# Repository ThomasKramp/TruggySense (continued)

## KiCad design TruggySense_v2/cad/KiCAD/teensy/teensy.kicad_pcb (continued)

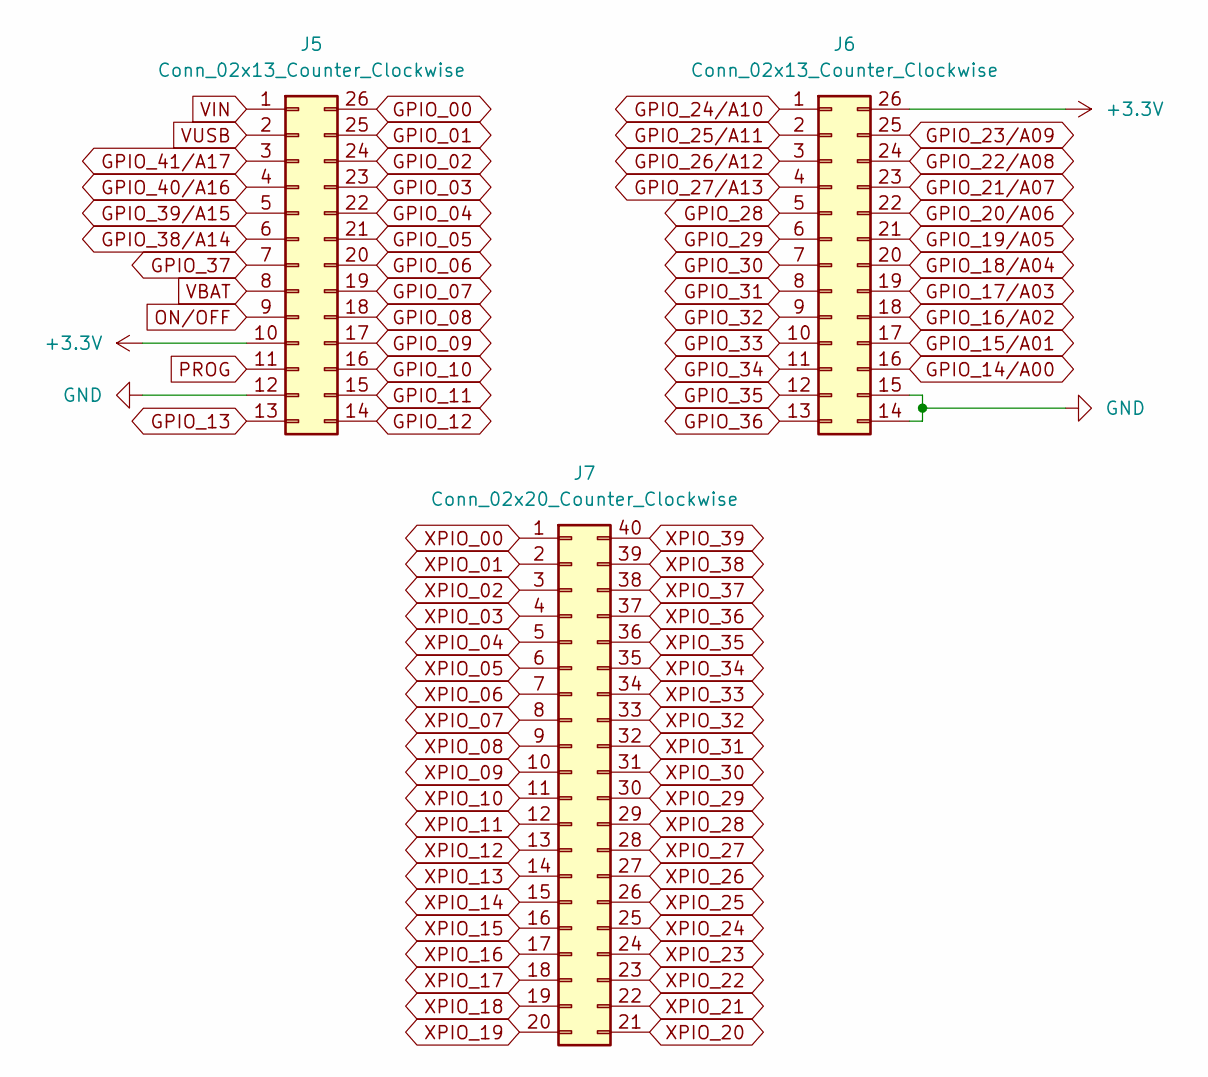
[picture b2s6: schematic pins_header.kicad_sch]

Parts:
J5, J6: Conn_02x13_Counter_Clockwise; PinSocket_2x13_P2.54mm_Vertical
J7: Conn_02x20_Counter_Clockwise; PinHeader_2x20_P2.54mm_Vertical

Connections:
+3.3V: J5.10, J6.26; also elsewhere on the board
FLS_32_B2: J5.11; also elsewhere on the board
GND: J5.12, J6.14, J6.15; also elsewhere on the board
GPIO_00: J5.26; also elsewhere on the board
GPIO_01: J5.25; also elsewhere on the board
GPIO_02: J5.24; also elsewhere on the board
GPIO_03: J5.23; also elsewhere on the board
GPIO_04: J5.22; also elsewhere on the board
GPIO_05: J5.21; also elsewhere on the board
GPIO_06: J5.20; also elsewhere on the board
GPIO_07: J5.19; also elsewhere on the board
GPIO_08: J5.18; also elsewhere on the board
GPIO_09: J5.17; also elsewhere on the board
GPIO_10: J5.16; also elsewhere on the board
GPIO_11: J5.15; also elsewhere on the board
GPIO_12: J5.14; also elsewhere on the board
GPIO_13: J5.13; also elsewhere on the board
GPIO_14/A00: J6.16; also elsewhere on the board
GPIO_15/A01: J6.17; also elsewhere on the board
GPIO_16/A02: J6.18; also elsewhere on the board
GPIO_17/A03: J6.19; also elsewhere on the board
GPIO_18/A04: J6.20; also elsewhere on the board
GPIO_19/A05: J6.21; also elsewhere on the board
GPIO_20/A06: J6.22; also elsewhere on the board
GPIO_21/A07: J6.23; also elsewhere on the board
GPIO_22/A08: J6.24; also elsewhere on the board
GPIO_23/A09: J6.25; also elsewhere on the board
GPIO_24/A10: J6.1; also elsewhere on the board
GPIO_25/A11: J6.2; also elsewhere on the board
GPIO_26/A12: J6.3; also elsewhere on the board
GPIO_27/A13: J6.4; also elsewhere on the board
GPIO_28: J6.5; also elsewhere on the board
GPIO_29: J6.6; also elsewhere on the board
GPIO_30: J6.7; also elsewhere on the board
GPIO_31: J6.8; also elsewhere on the board
GPIO_32: J6.9; also elsewhere on the board
GPIO_33: J6.10; also elsewhere on the board
GPIO_34: J6.11; also elsewhere on the board
GPIO_35: J6.12; also elsewhere on the board
GPIO_36: J6.13; also elsewhere on the board
GPIO_37: J5.7; also elsewhere on the board
GPIO_38/A14: J5.6; also elsewhere on the board
GPIO_39/A15: J5.5; also elsewhere on the board
GPIO_40/A16: J5.4; also elsewhere on the board
GPIO_41/A17: J5.3; also elsewhere on the board
ON/OFF: J5.9; also elsewhere on the board
VBAT: J5.8; also elsewhere on the board
VIN: J5.1; also elsewhere on the board
VUSB: J5.2; also elsewhere on the board
XPIO_00: J7.1; also elsewhere on the board
XPIO_01: J7.2; also elsewhere on the board
XPIO_02: J7.3; also elsewhere on the board
XPIO_03: J7.4; also elsewhere on the board
XPIO_04: J7.5; also elsewhere on the board
XPIO_05: J7.6; also elsewhere on the board
XPIO_06: J7.7; also elsewhere on the board
XPIO_07: J7.8; also elsewhere on the board
XPIO_08: J7.9; also elsewhere on the board
XPIO_09: J7.10; also elsewhere on the board
XPIO_10: J7.11; also elsewhere on the board
XPIO_11: J7.12; also elsewhere on the board
XPIO_12: J7.13; also elsewhere on the board
XPIO_13: J7.14; also elsewhere on the board
XPIO_14: J7.15; also elsewhere on the board
XPIO_15: J7.16; also elsewhere on the board
XPIO_16: J7.17; also elsewhere on the board
XPIO_17: J7.18; also elsewhere on the board
XPIO_18: J7.19; also elsewhere on the board
XPIO_19: J7.20; also elsewhere on the board
XPIO_20: J7.21; also elsewhere on the board
XPIO_21: J7.22; also elsewhere on the board
XPIO_22: J7.23; also elsewhere on the board
XPIO_23: J7.24; also elsewhere on the board
XPIO_24: J7.25; also elsewhere on the board
XPIO_25: J7.26; also elsewhere on the board
XPIO_26: J7.27; also elsewhere on the board
XPIO_27: J7.28; also elsewhere on the board
XPIO_28: J7.29; also elsewhere on the board
XPIO_29: J7.30; also elsewhere on the board
XPIO_30: J7.31; also elsewhere on the board
XPIO_31: J7.32; also elsewhere on the board
XPIO_32: J7.33; also elsewhere on the board
XPIO_33: J7.34; also elsewhere on the board
XPIO_34: J7.35; also elsewhere on the board
XPIO_35: J7.36; also elsewhere on the board
XPIO_36: J7.37; also elsewhere on the board
XPIO_37: J7.38; also elsewhere on the board
XPIO_38: J7.39; also elsewhere on the board
XPIO_39: J7.40; also elsewhere on the board

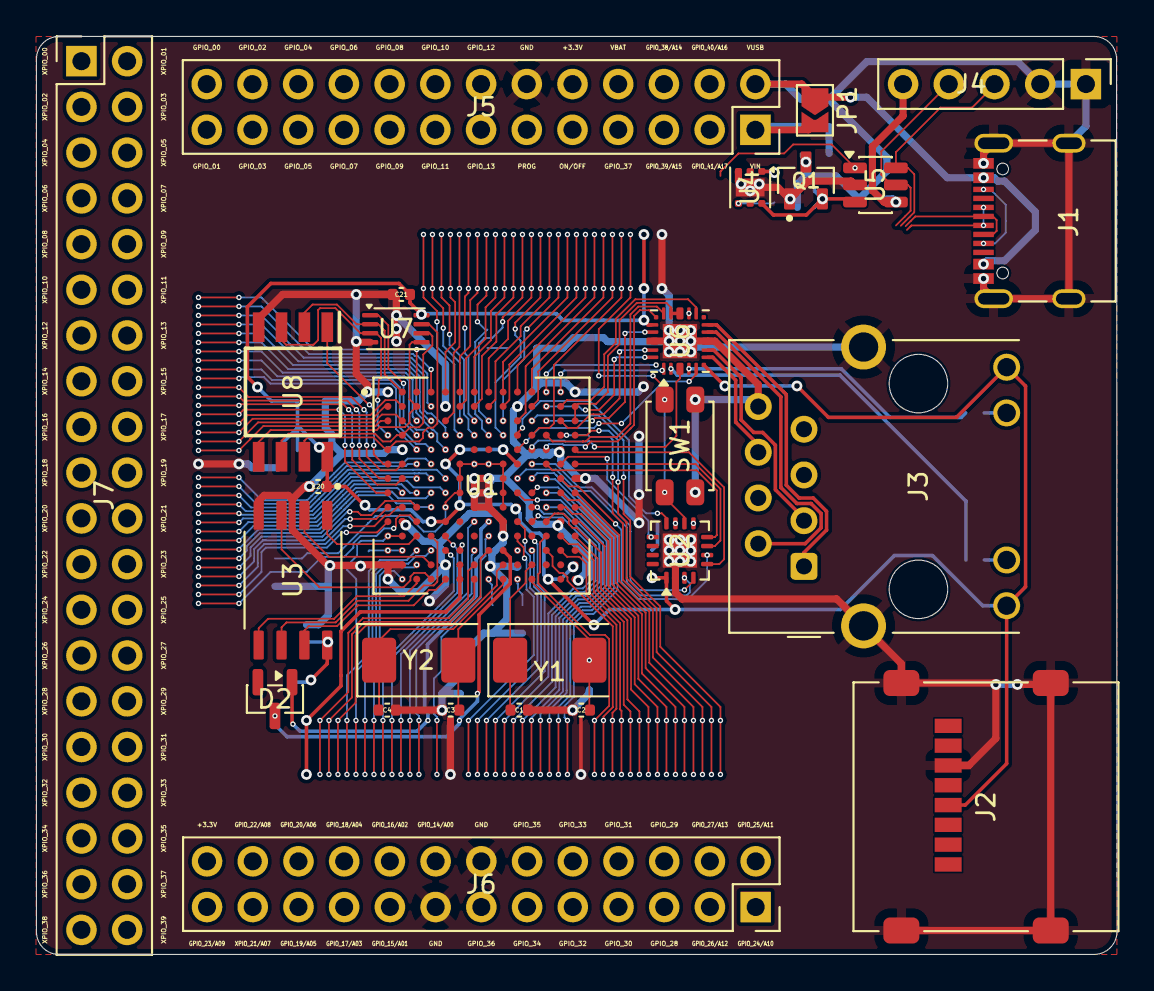
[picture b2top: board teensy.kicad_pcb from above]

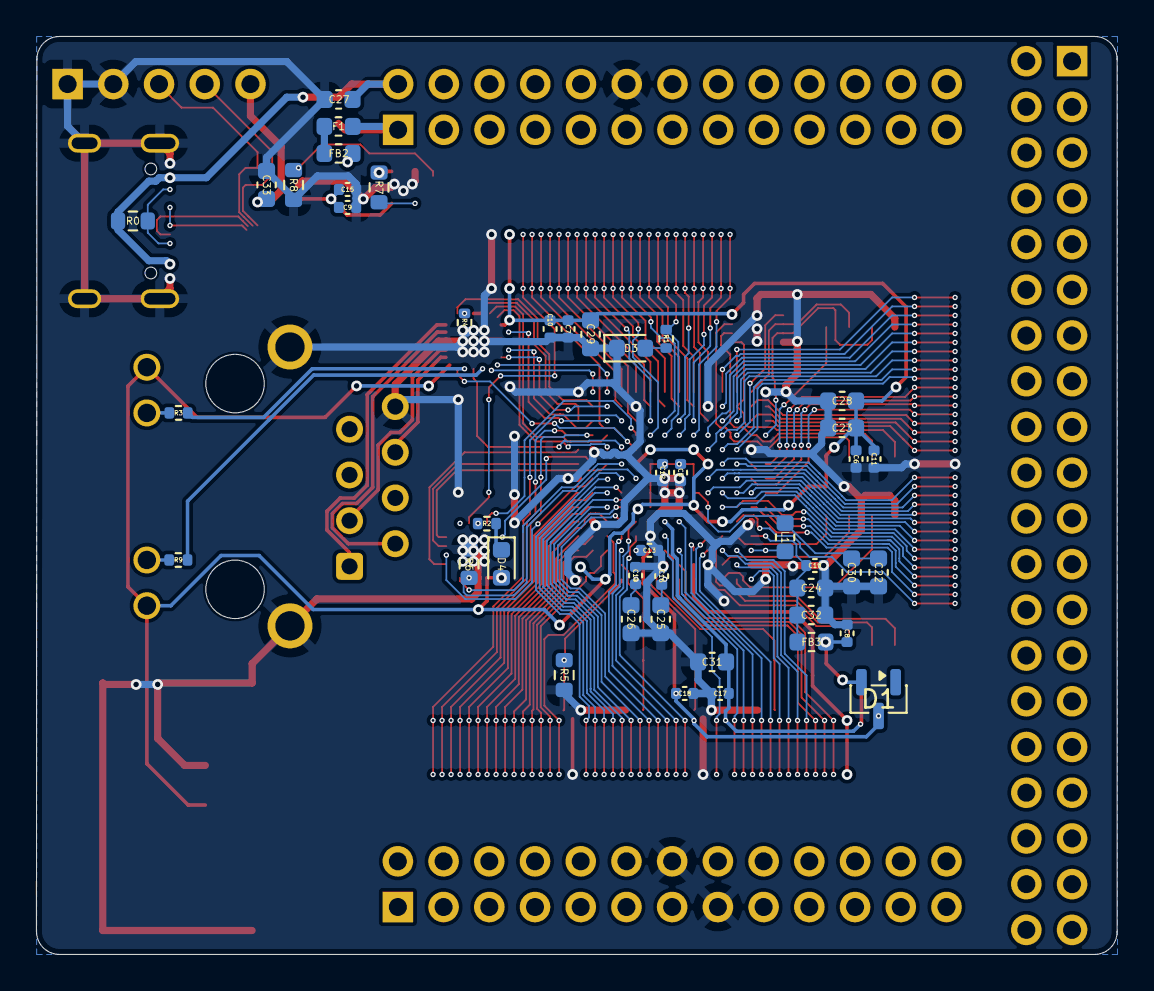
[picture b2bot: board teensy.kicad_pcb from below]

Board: 2 copper layers, 60.0 x 51.0 mm, 71 parts (44 on the bottom side), 164 nets.

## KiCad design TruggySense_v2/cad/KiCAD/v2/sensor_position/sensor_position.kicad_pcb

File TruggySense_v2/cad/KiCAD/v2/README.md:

## KiCAD

- **1_logic_board**:        The board-design and electrical schematic that contains the LLC, most sensors and connector points.
- **2_power_board**:        The board-design and electrical schematic that contains the connection to the battery and provides power to the motors.
- **sensor_position**:      The board-design and electrical schematic of the GNSS/GPS module.
- **sensor_temperature**:   The board-design and electrical schematic of the temperature sensor.

- **io_protection_buffer**: An electrical schematic of the protection buffer, for certain input purposes, used in the logic board.
- **io_protection_input**:  An electrical schematic for the input protection, used in the logic board.
- **io_protection_output**: An electrical schematic for the output protection, used in the logic board.

- **layout_nrf24l01**:      A generic board-layout for nRF24L01 modules, used in the logic board.
- **layout_pim448**:        A generic board-layout for motion sensor, used in the logic board.

- **recreation_ina219**:    A recreation of both the electrical schematic and board-design, for the low-current sensor.
- **recreation_lm2596**:    A recreation of both the electrical schematic and board-design, for the voltage converter (5V --> 3V3).

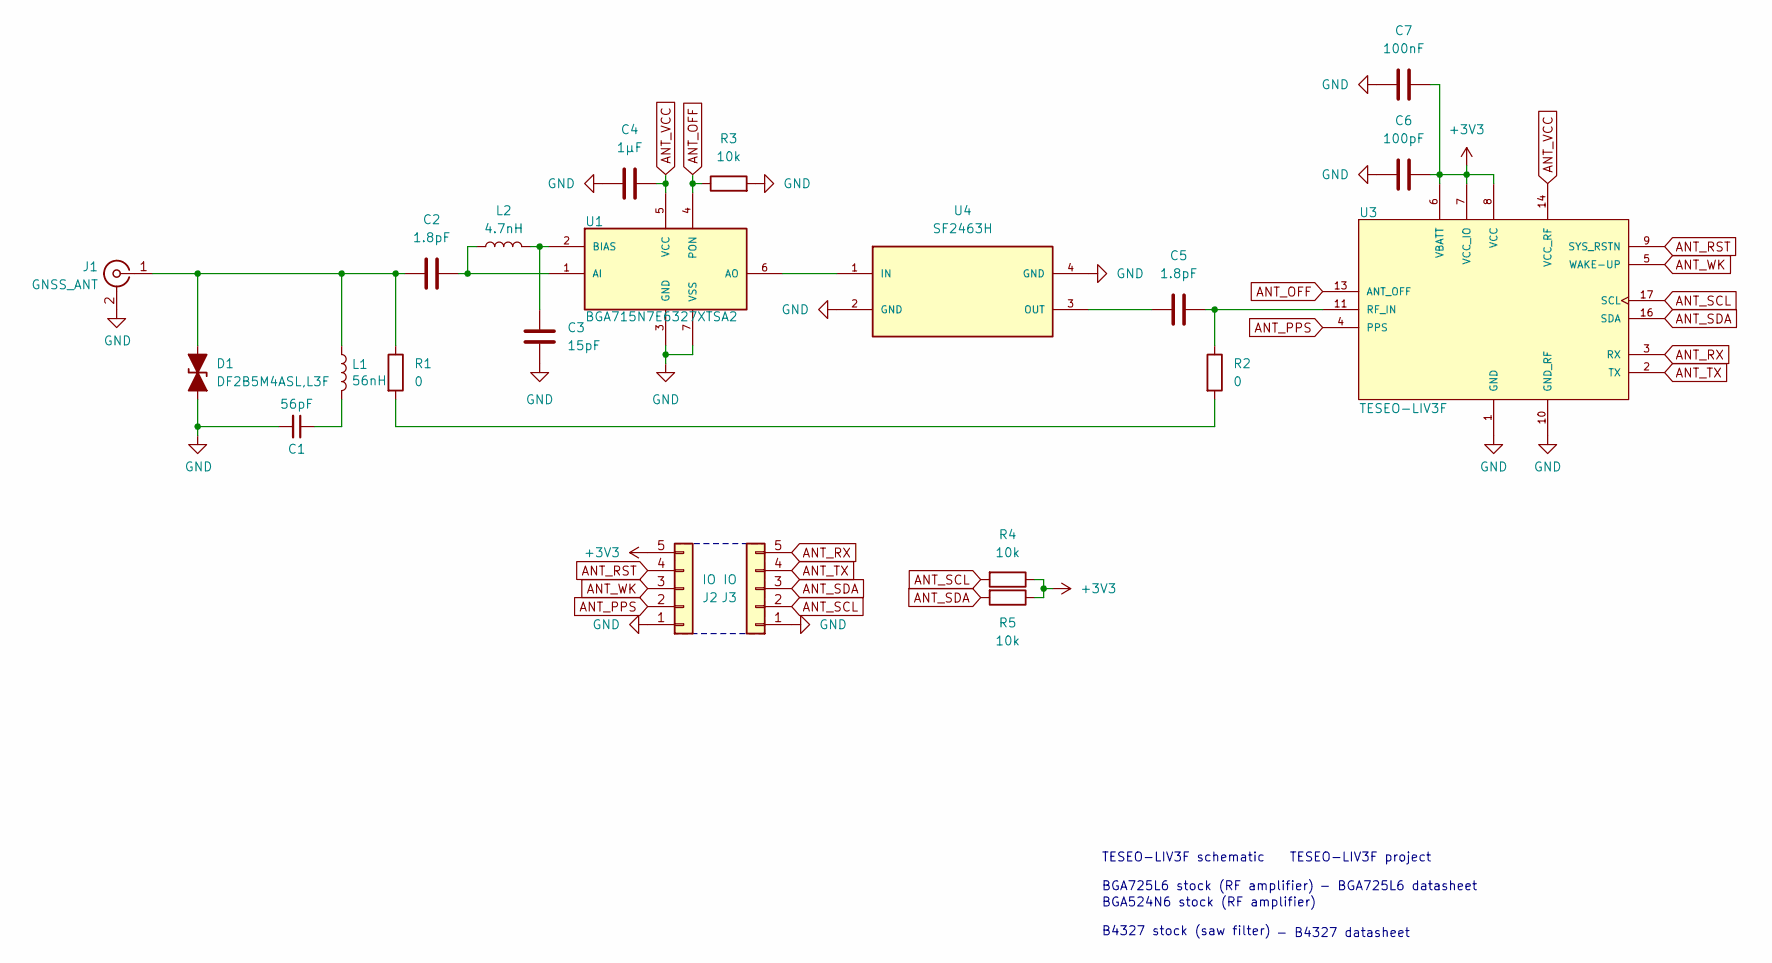
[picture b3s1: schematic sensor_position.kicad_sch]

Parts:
C1: 56pF; C_0805_2012Metric_Pad1.18x1.45mm_HandSolder; MPN GRM1555C1H560JA01D; Digi-Key_PN 490-1288-1-ND
C2, C5: 1.8pF; C_0805_2012Metric_Pad1.18x1.45mm_HandSolder
C3: 15pF; C_0805_2012Metric_Pad1.18x1.45mm_HandSolder
C4: 1µF; C_0805_2012Metric_Pad1.18x1.45mm_HandSolder
C6: 100pF; C_0805_2012Metric_Pad1.18x1.45mm_HandSolder
C7: 100nF; C_0805_2012Metric_Pad1.18x1.45mm_HandSolder
D1: DF2B5M4ASL,L3F; DF2B5M4ASL
J1: GNSS_ANT; SMA_Molex_73251-1153_EdgeMount_Horizontal
J2, J3: IO; PinHeader_1x05_P2.54mm_Vertical
L1: 56nH; L_0805_2012Metric_Pad1.05x1.20mm_HandSolder; MPN 744784156A; Digi-Key_PN 732-6242-1-ND
L2: 4.7nH; L_0805_2012Metric_Pad1.05x1.20mm_HandSolder
R1, R2: 0; R_0805_2012Metric_Pad1.20x1.40mm_HandSolder
R3, R4, R5: 10k; R_0805_2012Metric_Pad1.20x1.40mm_HandSolder
U1: BGA715N7E6327XTSA2; AMP_BGA715N7
U3: TESEO-LIV3F
U4: SF2463H

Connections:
+3V3: C6.2, C7.1, J2.5, R4.1, R5.1, U3.6 (VBATT), U3.7 (VCC_IO), U3.8 (VCC)
ANT_OFF: R3.1, U1.4 (PON), U3.13 (ANT_OFF)
ANT_PPS: J2.2, U3.4 (PPS)
ANT_RST: J2.4, U3.9 (SYS_RSTN)
ANT_RX: J3.5, U3.3 (RX)
ANT_SCL: J3.2, R4.2, U3.17 (SCL)
ANT_SDA: J3.3, R5.2, U3.16 (SDA)
ANT_TX: J3.4, U3.2 (TX)
ANT_VCC: C4.2, U1.5 (VCC), U3.14 (VCC_RF)
ANT_WK: J2.3, U3.5 (WAKE-UP)
GND: C1.2, C3.1, C4.1, C6.1, C7.2, D1.1 (A1), J1.2 (Ext), J2.1, J3.1, R3.2, U1.3 (GND), U1.7 (VSS), U3.1 (GND), U3.10 (GND_RF), U3.12 (GND_RF), U4.2 (GND), U4.4 (GND)
unnamed: C1.1, L1.2
unnamed: C2.1, D1.2 (A2), J1.1 (In), L1.1, R1.1
unnamed: R1.2, R2.2
unnamed: C2.2, L2.1, U1.1 (AI)
unnamed: U1.6 (AO), U4.1 (IN)
unnamed: C3.2, L2.2, U1.2 (BIAS)
unnamed: C5.2, R2.1, U3.11 (RF_IN)
unnamed: C5.1, U4.3 (OUT)

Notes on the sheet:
BGA725L6 stock (RF amplifier)
- BGA725L6 datasheet
BGA524N6 stock (RF amplifier)
TESEO-LIV3F project
B4327 stock (saw filter)
- B4327 datasheet
TESEO-LIV3F schematic

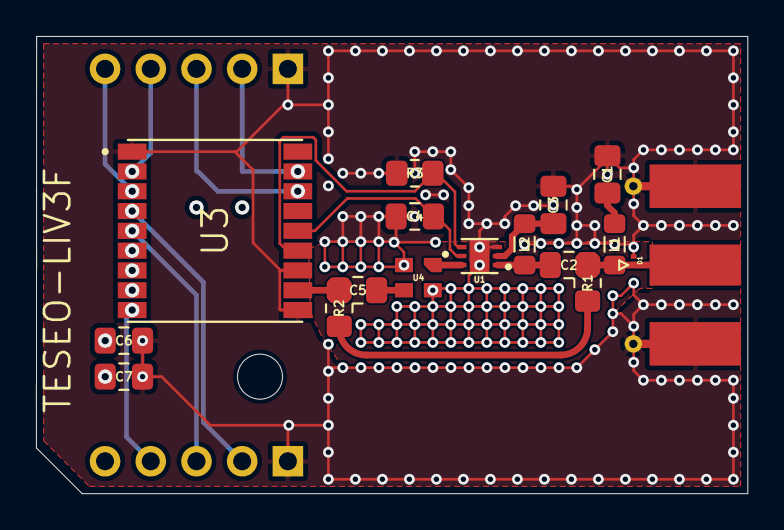
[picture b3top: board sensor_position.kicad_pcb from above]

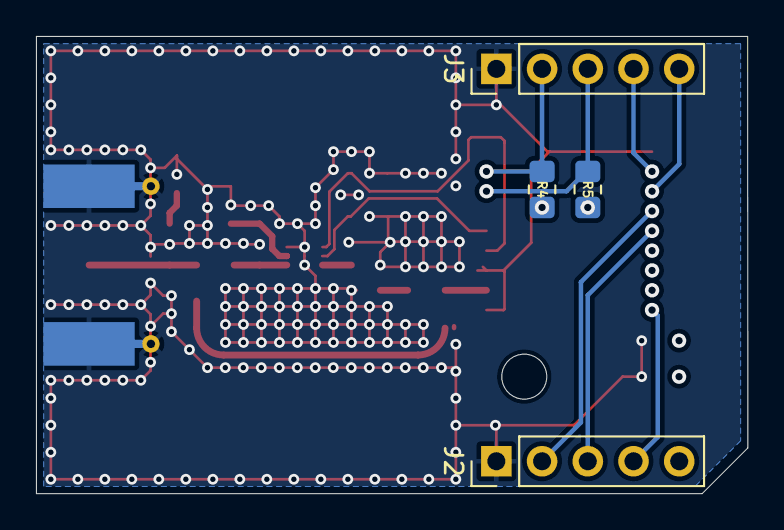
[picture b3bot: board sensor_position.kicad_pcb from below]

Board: 4 copper layers, 39.5 x 25.4 mm, 21 parts (4 on the bottom side), 19 nets.

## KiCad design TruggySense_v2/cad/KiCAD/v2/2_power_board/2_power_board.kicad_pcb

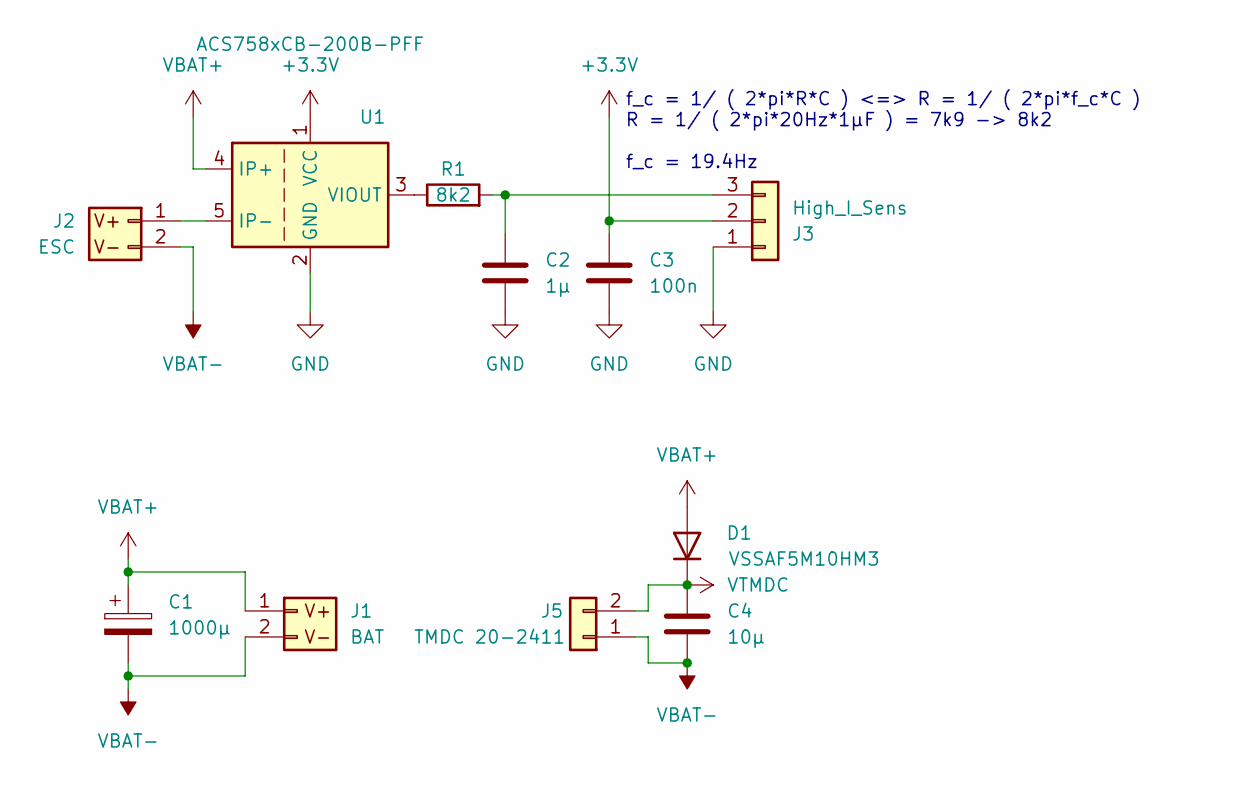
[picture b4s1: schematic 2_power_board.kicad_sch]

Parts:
C1: 1000µ; CP_Radial_D16.0mm_P7.50mm
C2: 1µ; C_0805_2012Metric_Pad1.18x1.45mm_HandSolder
C3: 100n; C_0805_2012Metric_Pad1.18x1.45mm_HandSolder
C4: 10µ; C_0805_2012Metric_Pad1.18x1.45mm_HandSolder
D1: VSSAF5M10HM3; DIOM5226X100N
J1: BAT; EC5_cable_pads
J2: ESC; EC5_cable_pads
J3: High_I_Sens; JST_XH_B3B-XH-A_1x03_P2.50mm_Vertical
J5: TMDC 20-2411; TerminalBlock_Phoenix_MKDS-1,5-2-5.08_1x02_P5.08mm_Horizont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
R1: 8k2; R_0805_2012Metric_Pad1.20x1.40mm_HandSolder
U1: ACS758xCB-200B-PFF; Allegro_CB_PFF

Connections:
+3.3V: C3.2, J3.2, U1.1 (VCC)
GND: C2.1, C3.1, J3.1, U1.2 (GND)
unnamed: J2.1 (V+), U1.5 (IP-)
unnamed: C2.2, J3.3, R1.2
unnamed: R1.1, U1.3 (VIOUT)
VBAT+: C1.1, D1.2 (A), J1.1 (V+), U1.4 (IP+)
VBAT-: C1.2, C4.2, J1.2 (V-), J2.2 (V-), J5.1
VTMDC: C4.1, D1.1 (K), J5.2

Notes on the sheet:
f_c = 1/ ( 2*pi*R*C ) <=> R = 1/ ( 2*pi*f_c*C ) R = 1/ ( 2*pi*20Hz*1µF ) = 7k9 -> 8k2 f_c = 19.4Hz

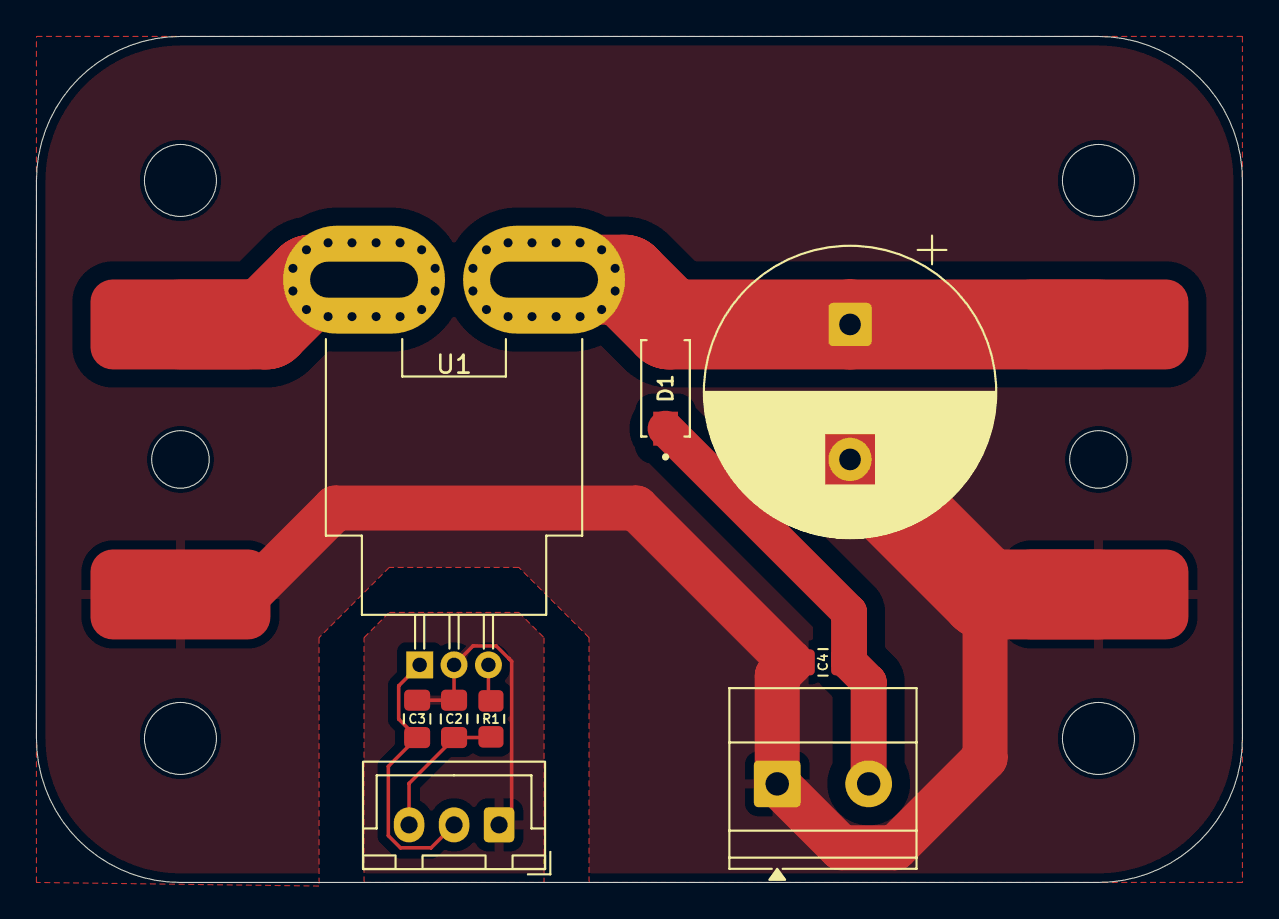
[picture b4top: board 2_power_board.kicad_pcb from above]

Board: 2 copper layers, 67.0 x 47.0 mm, 11 parts (0 on the bottom side), 8 nets.

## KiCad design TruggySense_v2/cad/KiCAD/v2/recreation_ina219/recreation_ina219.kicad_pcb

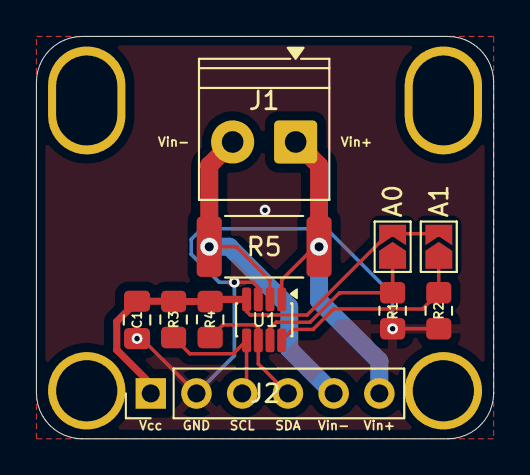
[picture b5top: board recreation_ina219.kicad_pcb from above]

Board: 2 copper layers, 25.4 x 22.4 mm, 11 parts (0 on the bottom side), 8 nets.

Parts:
C1: 100nF; C_0805_2012Metric_Pad1.18x1.45mm_HandSolder
J1: IN; TerminalBlock_Phoenix_PT-1,5-2-3.5-H_1x02_P3.50mm_Horizontal
J2: IO; PinHeader_1x06_P2.54mm_Vertical
JP1: A0; SolderJumper-2_P1.3mm_Open_TrianglePad1.0x1.5mm
JP2: A1; SolderJumper-2_P1.3mm_Open_TrianglePad1.0x1.5mm
R1, R2: 10k; R_0805_2012Metric_Pad1.20x1.40mm_HandSolder
R3, R4: 4k7; R_0805_2012Metric_Pad1.20x1.40mm_HandSolder
R5: 100m; R_2512_6332Metric_Pad1.40x3.35mm_HandSolder
U1: INA219AxDCN; SOT-23-8

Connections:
+3V3: C1.1, J2.1, JP1.2 (B), JP2.2 (B), R3.1, R4.1, U1.4 (VS)
GND: C1.2, J2.2, R1.2, R2.2, U1.3 (GND)
IN+: J1.1, J2.6, R5.1, U1.1 (IN+)
IN-: J1.2, J2.5, R5.2, U1.2 (IN-)
unnamed: JP1.1 (A), R1.1, U1.7 (A0)
unnamed: JP2.1 (A), R2.1, U1.8 (A1)
SCL: J2.3, R3.2, U1.5 (SCL)
SDA: J2.4, R4.2, U1.6 (SDA)

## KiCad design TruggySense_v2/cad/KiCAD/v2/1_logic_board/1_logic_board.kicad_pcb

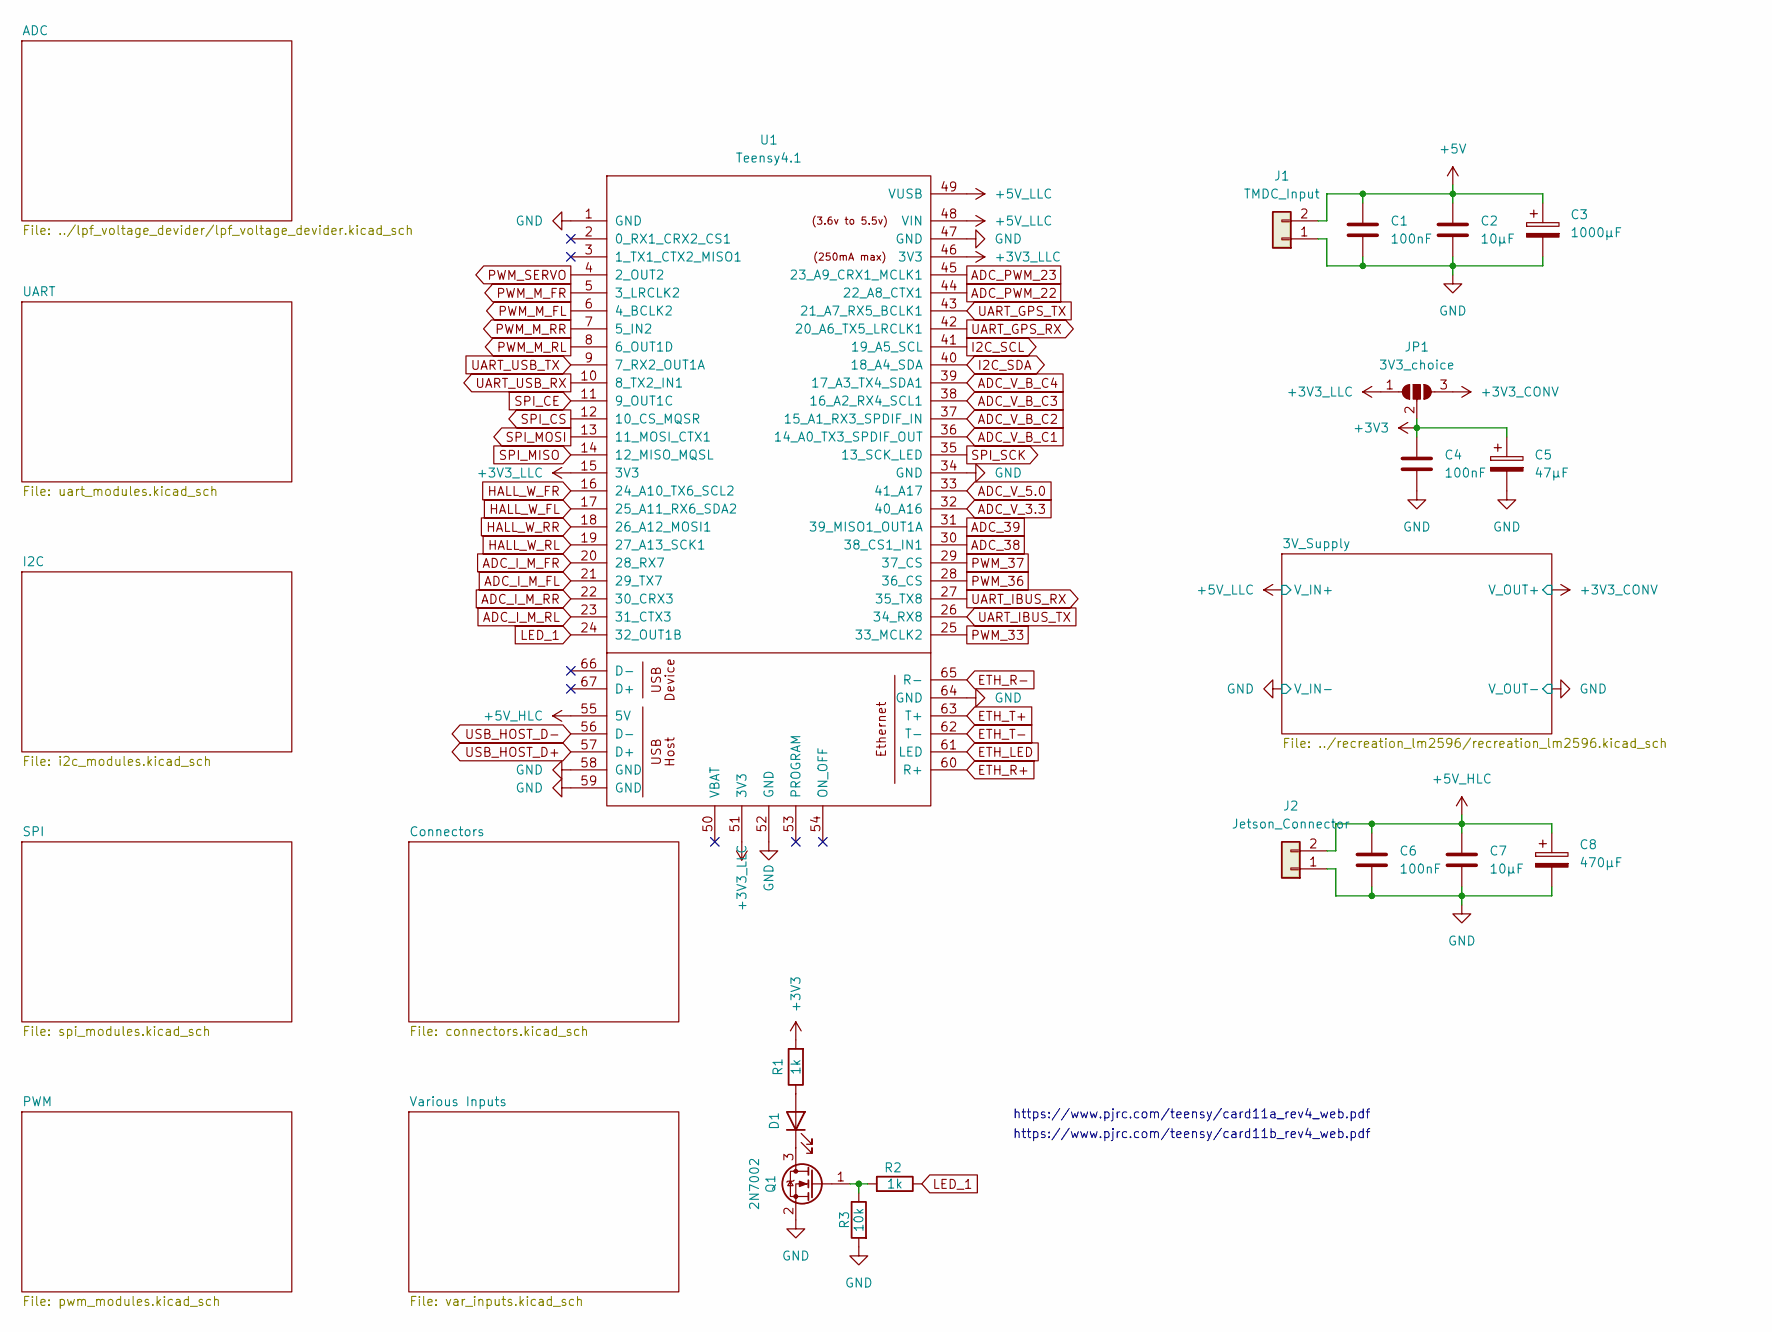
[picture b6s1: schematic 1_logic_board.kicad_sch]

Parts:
C1, C4, C6: 100nF; C_0805_2012Metric_Pad1.18x1.45mm_HandSolder
C2, C7: 10µF; C_0805_2012Metric_Pad1.18x1.45mm_HandSolder
C3: 1000µF; CP_Radial_D10.0mm_P5.00mm
C5: 47µF; CP_Radial_D8.0mm_P3.50mm
C8: 470µF; CP_Radial_D10.0mm_P5.00mm
D1: LED; LED_PLCC-2_3.4x3.0mm_AK
J1: TMDC_Input; TerminalBlock_Phoenix_MKDS-1,5-2-5.08_1x02_P5.08mm_Horizont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
J2: Jetson_Connector; TerminalBlock_Phoenix_MKDS-1,5-2-5.08_1x02_P5.08mm_Horizont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
JP1: 3V3_choice; SolderJumper-3_P2.0mm_Open_TrianglePad1.0x1.5mm_NumberLabels
Q1: 2N7002; SOT-23
R1, R2: 1k; R_0805_2012Metric_Pad1.20x1.40mm_HandSolder
R3: 10k; R_0805_2012Metric_Pad1.20x1.40mm_HandSolder
U1: Teensy4.1; Teensy41

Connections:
+3V3: C4.1, C5.1, JP1.2 (C), R1.2; also elsewhere on the board
+3V3_CONV: JP1.3 (B); also elsewhere on the board
+3V3_LLC: JP1.1 (A), U1.15 (3V3), U1.46 (3V3), U1.51 (3V3)
+5V: C1.1, C2.1, C3.1, J1.2; also elsewhere on the board
+5V_HLC: C6.1, C7.1, C8.1, J2.2, U1.55 (5V); also elsewhere on the board
+5V_LLC: U1.48 (VIN), U1.49 (VUSB); also elsewhere on the board
ADC_38: U1.30 (38_CS1_IN1); also elsewhere on the board
ADC_39: U1.31 (39_MISO1_OUT1A); also elsewhere on the board
ADC_I_M_FL: U1.21 (29_TX7); also elsewhere on the board
ADC_I_M_FR: U1.20 (28_RX7); also elsewhere on the board
ADC_I_M_RL: U1.23 (31_CTX3); also elsewhere on the board
ADC_I_M_RR: U1.22 (30_CRX3); also elsewhere on the board
ADC_PWM_22: U1.44 (22_A8_CTX1); also elsewhere on the board
ADC_PWM_23: U1.45 (23_A9_CRX1_MCLK1); also elsewhere on the board
ADC_V_3.3: U1.32 (40_A16); also elsewhere on the board
ADC_V_5.0: U1.33 (41_A17); also elsewhere on the board
ADC_V_B_C1: U1.36 (14_A0_TX3_SPDIF_OUT); also elsewhere on the board
ADC_V_B_C2: U1.37 (15_A1_RX3_SPDIF_IN); also elsewhere on the board
ADC_V_B_C3: U1.38 (16_A2_RX4_SCL1); also elsewhere on the board
ADC_V_B_C4: U1.39 (17_A3_TX4_SDA1); also elsewhere on the board
ETH_LED: U1.61 (LED); also elsewhere on the board
ETH_R+: U1.60 (R+); also elsewhere on the board
ETH_R-: U1.65 (R-); also elsewhere on the board
ETH_T+: U1.63 (T+); also elsewhere on the board
ETH_T-: U1.62 (T-); also elsewhere on the board
GND: C1.2, C2.2, C3.2, C4.2, C5.2, C6.2, C7.2, C8.2, J1.1, J2.1, Q1.2 (S), R3.2, U1.1 (GND), U1.34 (GND), U1.47 (GND), U1.52 (GND), U1.58 (GND), U1.59 (GND), U1.64 (GND); also elsewhere on the board
HALL_W_FL: U1.17 (25_A11_RX6_SDA2); also elsewhere on the board
HALL_W_FR: U1.16 (24_A10_TX6_SCL2); also elsewhere on the board
HALL_W_RL: U1.19 (27_A13_SCK1); also elsewhere on the board
HALL_W_RR: U1.18 (26_A12_MOSI1); also elsewhere on the board
I2C_SCL: U1.41 (19_A5_SCL); also elsewhere on the board
I2C_SDA: U1.40 (18_A4_SDA); also elsewhere on the board
LED_1: R2.1, U1.24 (32_OUT1B); also elsewhere on the board
unnamed: D1.2 (A), R1.1
unnamed: D1.1 (K), Q1.3 (D)
unnamed: Q1.1 (G), R2.2, R3.1
PWM_33: U1.25 (33_MCLK2); also elsewhere on the board
PWM_36: U1.28 (36_CS); also elsewhere on the board
PWM_37: U1.29 (37_CS); also elsewhere on the board
PWM_M_FL: U1.6 (4_BCLK2); also elsewhere on the board
PWM_M_FR: U1.5 (3_LRCLK2); also elsewhere on the board
PWM_M_RL: U1.8 (6_OUT1D); also elsewhere on the board
PWM_M_RR: U1.7 (5_IN2); also elsewhere on the board
PWM_SERVO: U1.4 (2_OUT2); also elsewhere on the board
SPI_CE: U1.11 (9_OUT1C); also elsewhere on the board
SPI_CS: U1.12 (10_CS_MQSR); also elsewhere on the board
SPI_MISO: U1.14 (12_MISO_MQSL); also elsewhere on the board
SPI_MOSI: U1.13 (11_MOSI_CTX1); also elsewhere on the board
SPI_SCK: U1.35 (13_SCK_LED); also elsewhere on the board
UART_GPS_RX: U1.42 (20_A6_TX5_LRCLK1); also elsewhere on the board
UART_GPS_TX: U1.43 (21_A7_RX5_BCLK1); also elsewhere on the board
UART_IBUS_RX: U1.27 (35_TX8); also elsewhere on the board
UART_IBUS_TX: U1.26 (34_RX8); also elsewhere on the board
UART_USB_RX: U1.10 (8_TX2_IN1); also elsewhere on the board
UART_USB_TX: U1.9 (7_RX2_OUT1A); also elsewhere on the board
USB_HOST_D+: U1.57 (D+); also elsewhere on the board
USB_HOST_D-: U1.56 (D-); also elsewhere on the board

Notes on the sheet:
https://www.pjrc.com/teensy/card11b_rev4_web.pdf
https://www.pjrc.com/teensy/card11a_rev4_web.pdf

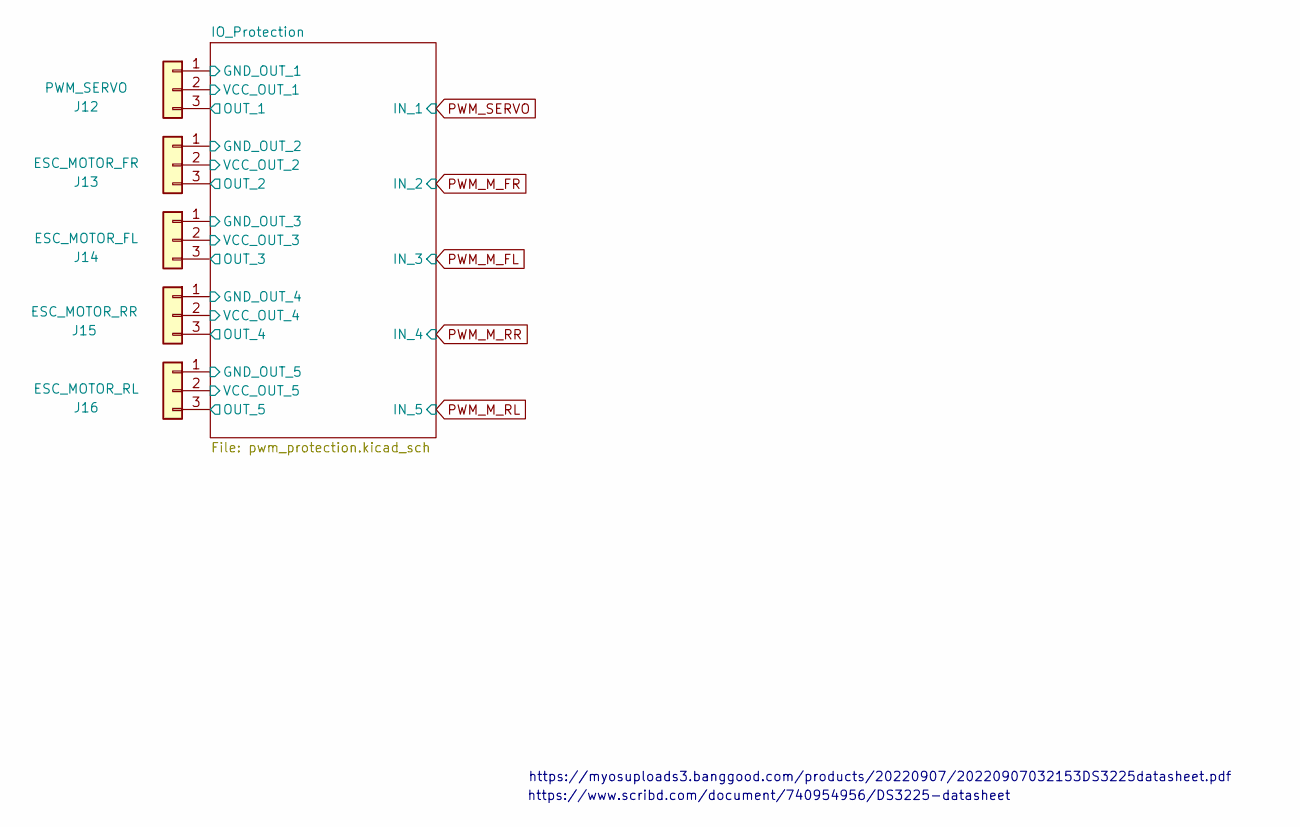
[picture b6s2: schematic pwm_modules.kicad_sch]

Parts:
J12: PWM_SERVO; JST_XH_B3B-XH-A_1x03_P2.50mm_Vertical
J13: ESC_MOTOR_FR; JST_XH_B3B-XH-A_1x03_P2.50mm_Vertical
J14: ESC_MOTOR_FL; JST_XH_B3B-XH-A_1x03_P2.50mm_Vertical
J15: ESC_MOTOR_RR; JST_XH_B3B-XH-A_1x03_P2.50mm_Vertical
J16: ESC_MOTOR_RL; JST_XH_B3B-XH-A_1x03_P2.50mm_Vertical

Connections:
/PWM/IO_Protection/GND_OUT_1: J12.1; also elsewhere on the board
/PWM/IO_Protection/GND_OUT_2: J13.1; also elsewhere on the board
/PWM/IO_Protection/GND_OUT_3: J14.1; also elsewhere on the board
/PWM/IO_Protection/GND_OUT_4: J15.1; also elsewhere on the board
/PWM/IO_Protection/GND_OUT_5: J16.1; also elsewhere on the board
/PWM/IO_Protection/OUT_1: J12.3; also elsewhere on the board
/PWM/IO_Protection/OUT_2: J13.3; also elsewhere on the board
/PWM/IO_Protection/OUT_3: J14.3; also elsewhere on the board
/PWM/IO_Protection/OUT_4: J15.3; also elsewhere on the board
/PWM/IO_Protection/OUT_5: J16.3; also elsewhere on the board
/PWM/IO_Protection/VCC_OUT_1: J12.2; also elsewhere on the board
/PWM/IO_Protection/VCC_OUT_2: J13.2; also elsewhere on the board
/PWM/IO_Protection/VCC_OUT_3: J14.2; also elsewhere on the board
/PWM/IO_Protection/VCC_OUT_4: J15.2; also elsewhere on the board
/PWM/IO_Protection/VCC_OUT_5: J16.2; also elsewhere on the board

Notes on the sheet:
https://myosuploads3.banggood.com/products/20220907/20220907032153DS3225datasheet.pdf
https://www.scribd.com/document/740954956/DS3225-datasheet
